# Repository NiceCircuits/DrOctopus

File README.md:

DrOctopus
=========

Art project

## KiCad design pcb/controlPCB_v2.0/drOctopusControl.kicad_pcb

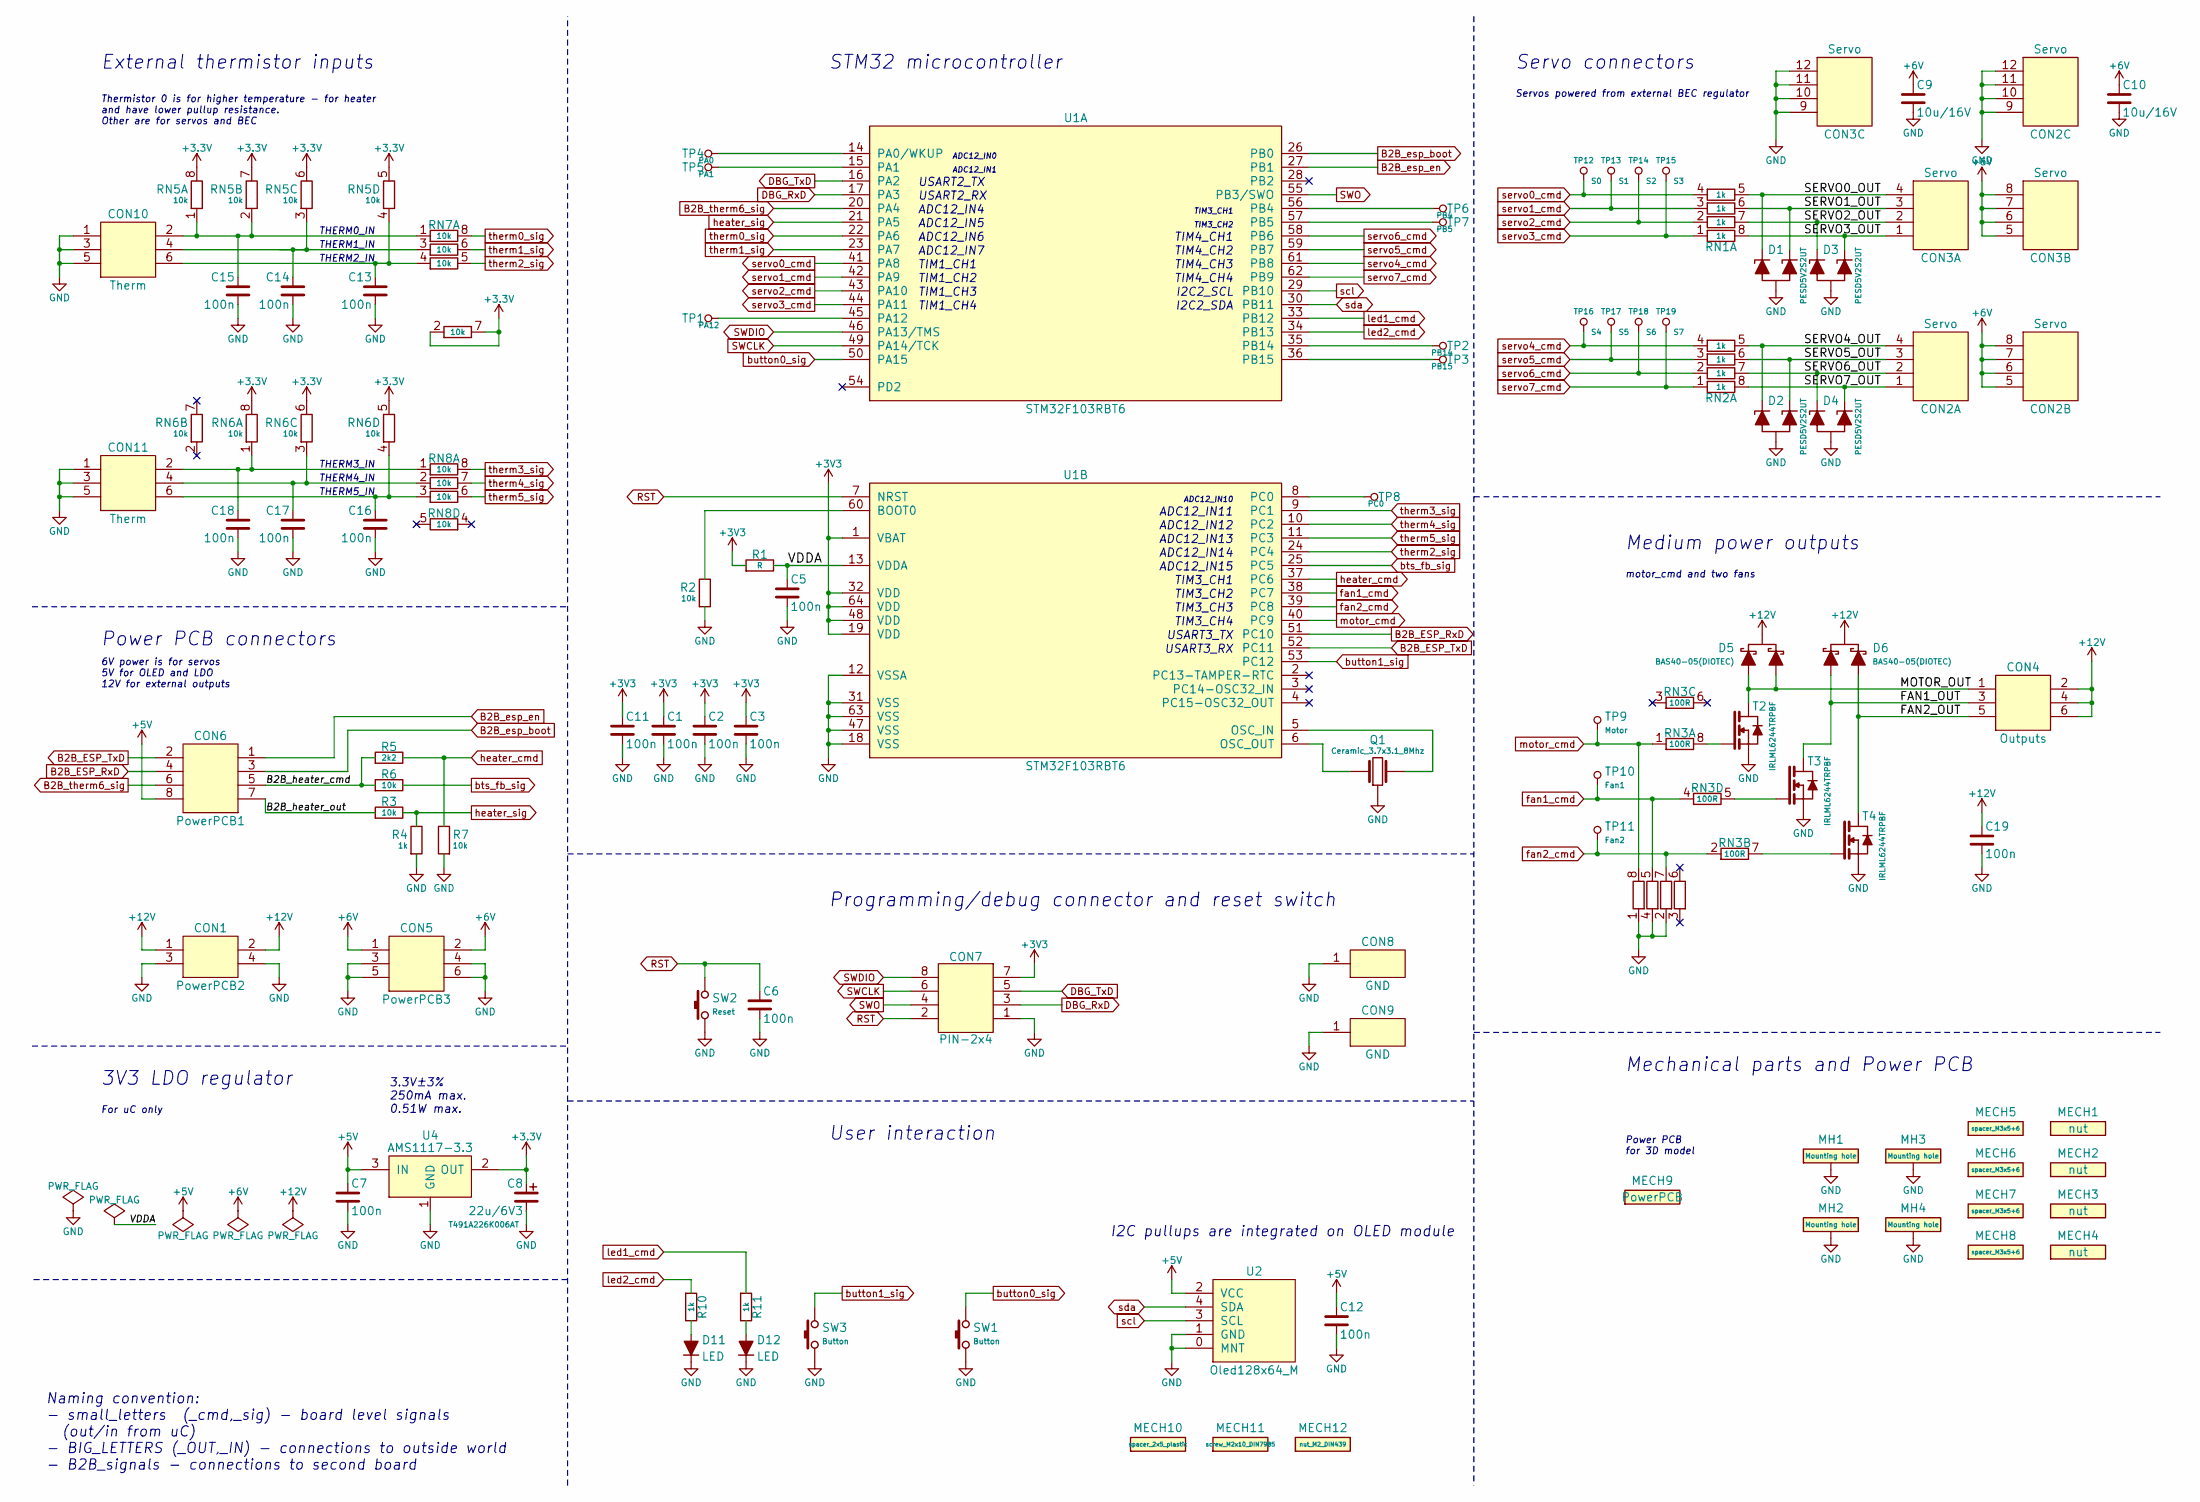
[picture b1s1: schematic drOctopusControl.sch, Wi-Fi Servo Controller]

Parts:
C1, C2, C3, C5, C6, C7, C11, C12, C13, C14, C15, C16, C17, C18, C19: 100n; 0603_N
C8: 22u/6V3; Tantal_A_N
C9, C10: 10u/16V; 0805_N
CON1: PowerPCB2; PIN-2x2_F_N
CON2, CON3: Servo; PIN-3x4_N
CON4: Outputs; PIN-2x3_N
CON5: PowerPCB3; PIN-2x3_F_N
CON6: PowerPCB1; PIN-2x4_F_N
CON7: PIN-2x4; PIN-2x4_N
CON8, CON9: GND; PIN-1x1_L
CON10, CON11: Therm; PIN-2x3_N
D1, D2, D3, D4: PESD5V2S2UT; SOT23-3_N
D5, D6: BAS40-05(DIOTEC); SOT23-3_N
D11, D12: LED; 0805_N
MECH1, MECH2, MECH3, MECH4: nut; nut_M3_DIN985
MECH5, MECH6, MECH7, MECH8: spacer_M3x5+6
MECH9: PowerPCB; dummy
MECH10: spacer_2x5_plastic
MECH11: screw_M2x10_DIN7985
MECH12: nut_M2_DIN439
MH1, MH2, MH3, MH4: Mounting hole; mounting_hole_3.2_7.5_plated_vias
Q1: Ceramic_3.7x3.1_8Mhz; 3.7x3.1_N
R1: R; 0603_R_N
R2, R3, R6, R7: 10k; 0603_R_N
R4, R10, R11: 1k; 0603_R_N
R5: 2k2; 0603_R_N
RN1, RN2: 1k; 4x0603_N
RN3: 100R; 4x0603_N
RN4, RN5, RN6, RN7, RN8: 10k; 4x0603_N
SW1, SW3: Button; MicroswitchSmd6x4_N
SW2: Reset; MicroswitchSmd6x4_N
T2, T3, T4: IRLML6244TRPBF; SOT23-3_N
TP1: PA12; TP_1mm
TP2: PB14; TP_1mm
TP3: PB15; TP_1mm
TP4: PA0; TP_1mm
TP5: PA1; TP_1mm
TP6: PB4; TP_1mm
TP7: PB5; TP_1mm
TP8: PC0; TP_1mm
TP9: Motor; TP_1mm
TP10: Fan1; TP_1mm
TP11: Fan2; TP_1mm
TP12: S0; TP_1mm
TP13: S1; TP_1mm
TP14: S2; TP_1mm
TP15: S3; TP_1mm
TP16: S4; TP_1mm
TP17: S5; TP_1mm
TP18: S6; TP_1mm
TP19: S7; TP_1mm
U1: STM32F103RBT6; QFP-64-0.5_N
U2: Oled128x64_M; Oled128x64_M_5.08N
U4: AMS1117-3.3; SOT223_N

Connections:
+5V: C7.1, C12.1, CON6.8, U2.2 (VCC), U4.3 (IN)
+6V: C9.1, C10.1, CON2.5 (1), CON2.6 (2), CON2.7 (3), CON2.8 (4), CON3.5 (1), CON3.6 (2), CON3.7 (3), CON3.8 (4), CON5.1, CON5.2
+12V: C19.1, CON1.1, CON1.2, CON4.2, CON4.4, CON4.6, D5.3 (C), D6.3 (C)
/B2B_heater_cmd: CON6.5, R5.1, R6.1
/B2B_heater_out: CON6.7, R3.1
/FAN1_OUT: CON4.3, D6.2 (A2), T3.3 (D)
/FAN2_OUT: CON4.5, D6.1 (A1), T4.3 (D)
/MOTOR_OUT: CON4.1, D5.1 (A1), D5.2 (A2), T2.3 (D)
/SERVO0_OUT: CON3.4, D1.2 (C2), RN1.5 (2)
/SERVO1_OUT: CON3.3, D1.1 (C1), RN1.6 (2)
/SERVO2_OUT: CON3.2, D3.2 (C2), RN1.7 (2)
/SERVO3_OUT: CON3.1, D3.1 (C1), RN1.8 (2)
/SERVO4_OUT: CON2.4, D2.2 (C2), RN2.5 (2)
/SERVO5_OUT: CON2.3, D2.1 (C1), RN2.6 (2)
/SERVO6_OUT: CON2.2, D4.2 (C2), RN2.7 (2)
/SERVO7_OUT: CON2.1, D4.1 (C1), RN2.8 (2)
/VDDA: C5.1, R1.2, U1.13 (VDDA)
B2B_ESP_RxD: CON6.4, U1.51 (PC10)
B2B_ESP_TxD: CON6.2, U1.52 (PC11)
B2B_esp_boot: CON6.3, U1.26 (PB0)
B2B_esp_en: CON6.1, U1.27 (PB1)
B2B_therm6_sig: CON6.6, U1.20 (PA4)
DBG_RxD: CON7.3, U1.17 (PA3)
DBG_TxD: CON7.5, U1.16 (PA2)
GND: C1.2, C2.2, C3.2, C5.2, C6.2, C7.2, C8.2, C9.2, C10.2, C11.2, C12.2, C13.2, C14.2, C15.2, C16.2, C17.2, C18.2, C19.2, CON1.3, CON1.4, CON2.9 (1), CON2.10 (2), CON2.11 (3), CON2.12 (4), CON3.9 (1), CON3.10 (2), CON3.11 (3), CON3.12 (4), CON5.3, CON5.4, CON5.5, CON5.6, CON7.1, CON8.1, CON9.1, CON10.1, CON10.3, CON10.5, CON11.1, CON11.3, CON11.5, D1.3 (A), D2.3 (A), D3.3 (A), D4.3 (A), D11.1 (A), D12.1 (A), MH1.1, MH2.1, MH3.1, MH4.1, Q1.2, R2.1, R4.1, R7.1, RN4.1, RN4.2 (1), RN4.4 (1), SW1.1, SW2.1, SW3.1, T2.2 (S), T3.2 (S), T4.2 (S), U1.12 (VSSA), U1.18 (VSS), U1.31 (VSS), U1.47 (VSS), U1.63 (VSS), U2.0 (MNT), U2.1 (GND), U4.1 (GND)
unnamed: C13.1, CON10.6, RN5.4 (1), RN7.4 (1)
unnamed: C14.1, CON10.4, RN5.3 (1), RN7.3 (1)
unnamed: C15.1, CON10.2, RN5.1, RN5.2 (1), RN7.1
unnamed: C16.1, CON11.6, RN6.4 (1), RN8.3 (1)
unnamed: C17.1, CON11.4, RN6.3 (1), RN8.2 (1)
unnamed: C18.1, CON11.2, RN6.1, RN8.1
unnamed: D11.2 (C), R10.2
unnamed: D12.2 (C), R11.2
unnamed: Q1.1, U1.6 (OSC_OUT)
unnamed: Q1.3, U1.5 (OSC_IN)
unnamed: R2.2, U1.60 (BOOT0)
unnamed: RN3.5 (2), T3.1 (G)
unnamed: RN3.7 (2), T4.1 (G)
unnamed: RN3.8 (2), T2.1 (G)
unnamed: TP1.1, U1.45 (PA12)
unnamed: TP2.1, U1.35 (PB14)
unnamed: TP3.1, U1.36 (PB15)
unnamed: TP4.1, U1.14 (PA0/WKUP)
unnamed: TP5.1, U1.15 (PA1)
unnamed: TP6.1, U1.56 (PB4)
unnamed: TP7.1, U1.57 (PB5)
unnamed: TP8.1, U1.8 (PC0)
RST: C6.1, CON7.2, SW2.2, U1.7 (NRST)
SWCLK: CON7.6, U1.49 (PA14/TCK)
SWDIO: CON7.8, U1.46 (PA13/TMS)
SWO: CON7.4, U1.55 (PB3/SWO)
bts_fb_sig: R6.2, U1.25 (PC5)
button0_sig: SW1.2, U1.50 (PA15)
button1_sig: SW3.2, U1.53 (PC12)
fan1_cmd: RN3.4 (1), RN4.5 (2), TP10.1, U1.38 (PC7)
fan2_cmd: RN3.2 (1), RN4.7 (2), TP11.1, U1.39 (PC8)
heater_cmd: R5.2, R7.2, U1.37 (PC6)
heater_sig: R3.2, R4.2, U1.21 (PA5)
led1_cmd: R11.1, U1.33 (PB12)
led2_cmd: R10.1, U1.34 (PB13)
motor_cmd: RN3.1, RN4.8 (2), TP9.1, U1.40 (PC9)
scl: U1.29 (PB10), U2.3 (SCL)
sda: U1.30 (PB11), U2.4 (SDA)
servo0_cmd: RN1.4 (1), TP12.1, U1.41 (PA8)
servo1_cmd: RN1.3 (1), TP13.1, U1.42 (PA9)
servo2_cmd: RN1.2 (1), TP14.1, U1.43 (PA10)
servo3_cmd: RN1.1, TP15.1, U1.44 (PA11)
servo4_cmd: RN2.4 (1), TP16.1, U1.61 (PB8)
servo5_cmd: RN2.3 (1), TP17.1, U1.59 (PB7)
servo6_cmd: RN2.2 (1), TP18.1, U1.58 (PB6)
servo7_cmd: RN2.1, TP19.1, U1.62 (PB9)
therm0_sig: RN7.8 (2), U1.22 (PA6)
therm1_sig: RN7.6 (2), U1.23 (PA7)
therm2_sig: RN7.5 (2), U1.24 (PC4)
therm3_sig: RN8.8 (2), U1.9 (PC1)
therm4_sig: RN8.7 (2), U1.10 (PC2)
therm5_sig: RN8.6 (2), U1.11 (PC3)

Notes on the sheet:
3.3V±3% 250mA max. 0.51W max.
ADC12_IN4
ADC12_IN5
ADC12_IN6
ADC12_IN7
ADC12_IN14
ADC12_IN15
ADC12_IN10
ADC12_IN11
ADC12_IN12
ADC12_IN13
USART2_TX
USART2_RX
I2C2_SCL
I2C2_SDA
TIM3_CH1
TIM3_CH2
TIM3_CH3
TIM3_CH4
TIM1_CH1
TIM1_CH2
TIM1_CH3
TIM1_CH4
USART3_TX
USART3_RX
TIM4_CH1
TIM4_CH2
TIM4_CH3
TIM4_CH4
THERM0_IN
THERM1_IN
THERM2_IN
THERM3_IN
THERM4_IN
THERM5_IN
External thermistor inputs
Thermistor 0 is for higher temperature - for heater and have lower pullup resistance. Other are for servos and BEC
Power PCB connectors
6V power is for servos 5V for OLED and LDO 12V for external outputs
3V3 LDO regulator

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
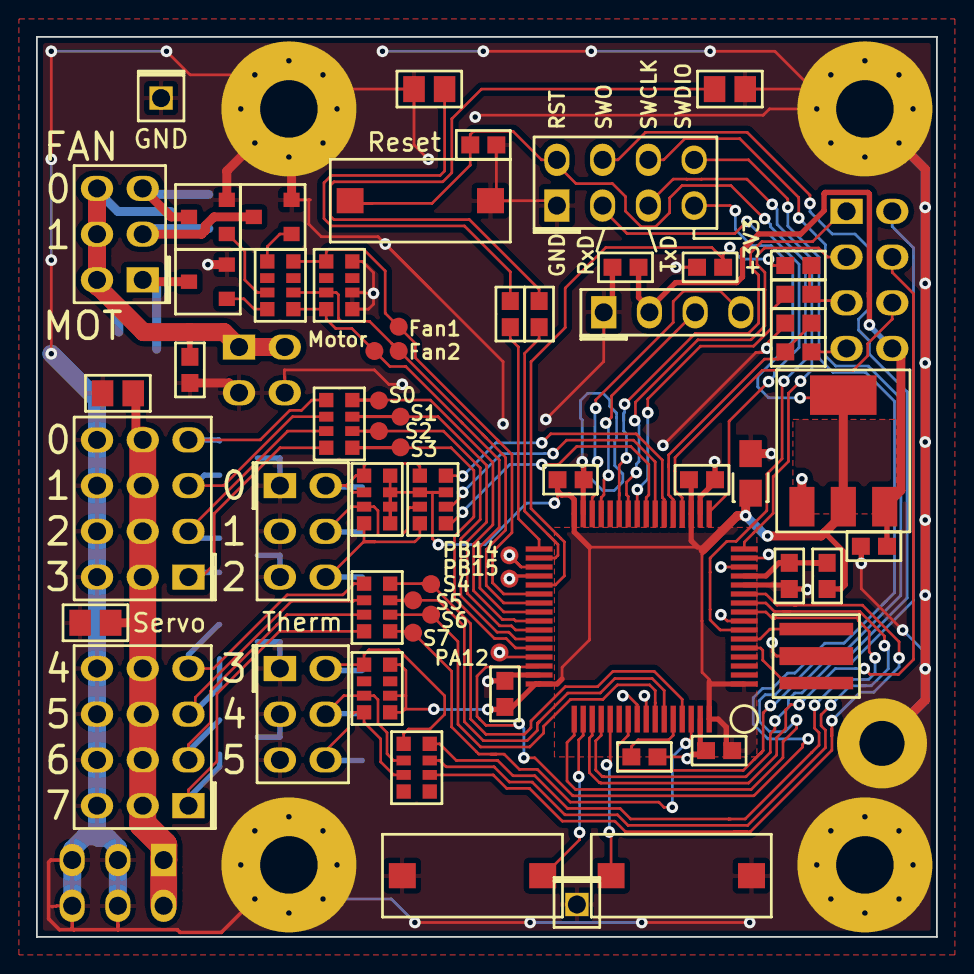
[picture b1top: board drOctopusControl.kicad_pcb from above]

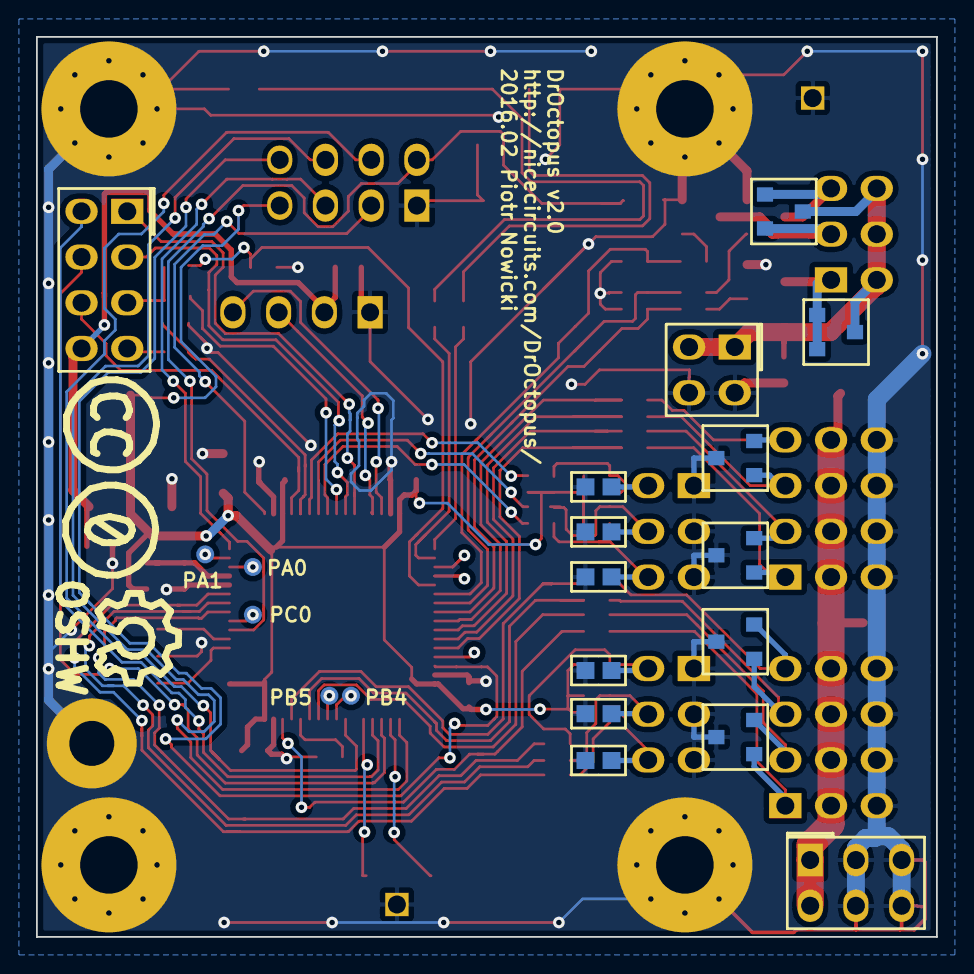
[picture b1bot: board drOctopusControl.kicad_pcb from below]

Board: 2 copper layers, 50.0 x 50.0 mm, 101 parts (27 on the bottom side), 78 nets.

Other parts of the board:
SYM: Symbol_OSHW-Logo_SilkScreen_07Jul2012; Symbol_OSHW-Logo_SilkScreen
Sym: Symbol_CreativeCommonsPublicDomain_SilkScreenTop_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; Symbol_CreativeCommonsPublicDomain_SilkScreenTop_SmallMinim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

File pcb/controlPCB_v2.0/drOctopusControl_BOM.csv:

Reference, Value, Footprint, Datasheet
RN1,1k,4x0603_N,
CON3,Servo,nicePinheaders:PIN-3x4_N,
CON2,Servo,nicePinheaders:PIN-3x4_N,
RN2,1k,4x0603_N,
U4,AMS1117-3.3,SOT223_N,
C7,100n,0603_N,
D1,PESD5V2S2UT,SOT23-3_N,
D3,PESD5V2S2UT,SOT23-3_N,
D2,PESD5V2S2UT,SOT23-3_N,
D4,PESD5V2S2UT,SOT23-3_N,
C9,10u/16V,0805_N,
C10,10u/16V,0805_N,
MH1,Mounting hole,mounting_hole_3.2_7.5_plated_vias,
C8,22u/6V3,Tantal_A_N,T491A226K006AT
MH2,Mounting hole,mounting_hole_3.2_7.5_plated_vias,
MH3,Mounting hole,mounting_hole_3.2_7.5_plated_vias,
MH4,Mounting hole,mounting_hole_3.2_7.5_plated_vias,
MECH1,nut,nut_M3_DIN985,
MECH2,nut,nut_M3_DIN985,
MECH3,nut,nut_M3_DIN985,
MECH4,nut,nut_M3_DIN985,
MECH5,spacer_M3x5+6,spacer_M3x5+6,
MECH6,spacer_M3x5+6,spacer_M3x5+6,
MECH7,spacer_M3x5+6,spacer_M3x5+6,
MECH8,spacer_M3x5+6,spacer_M3x5+6,
R10,1k,0603_R_N,
R11,1k,0603_R_N,
D12,LED,0805_N,
D11,LED,0805_N,
MECH9,PowerPCB,niceMechanical:dummy,
CON1,PowerPCB2,PIN-2x2_F_N,
CON5,PowerPCB3,PIN-2x3_F_N,
CON6,PowerPCB1,PIN-2x4_F_N,
CON10,Therm,PIN-2x3_N,
CON11,Therm,PIN-2x3_N,
CON4,Outputs,PIN-2x3_N,
D6,BAS40-05(DIOTEC),SOT23-3_N,
D5,BAS40-05(DIOTEC),SOT23-3_N,
RN3,100R,4x0603_N,
U2,Oled128x64_M,niceModules:Oled128x64_M_5.08N,
C1,100n,0603_N,
C2,100n,0603_N,
C3,100n,0603_N,
C5,100n,0603_N,
R1,R,0603_R_N,
U1,STM32F103RBT6,QFP-64-0.5_N,
C11,100n,0603_N,
C6,100n,0603_N,
Q1,Ceramic_3.7x3.1_8Mhz,3.7x3.1_N,
C15,100n,0603_N,
C14,100n,0603_N,
C13,100n,0603_N,
RN5,10k,4x0603_N,
C18,100n,0603_N,
C17,100n,0603_N,
C16,100n,0603_N,
RN6,10k,4x0603_N,
T3,IRLML6244TRPBF,SOT23-3_N,
T2,IRLML6244TRPBF,SOT23-3_N,
T4,IRLML6244TRPBF,SOT23-3_N,
SW1,Button,MicroswitchSmd6x4_N,
SW2,Reset,MicroswitchSmd6x4_N,
C12,100n,0603_N,
RN7,10k,4x0603_N,
RN8,10k,4x0603_N,
CON7,PIN-2x4,PIN-2x4_N,
C19,100n,0603_N,
R3,10k,0603_R_N,
R6,10k,0603_R_N,
R5,2k2,0603_R_N,
RN4,10k,4x0603_N,
R2,10k,0603_R_N,
R4,1k,0603_R_N,
R7,10k,0603_R_N,
TP2,PB14,pnConnector:TP_1mm,
TP3,PB15,pnConnector:TP_1mm,
TP4,PA0,pnConnector:TP_1mm,
TP5,PA1,pnConnector:TP_1mm,
TP8,PC0,pnConnector:TP_1mm,
TP6,PB4,pnConnector:TP_1mm,
TP7,PB5,pnConnector:TP_1mm,
TP1,PA12,pnConnector:TP_1mm,
CON9,GND,PIN-1x1_L,
CON8,GND,PIN-1x1_L,
TP9,Motor,pnConnector:TP_1mm,
TP10,Fan1,pnConnector:TP_1mm,
TP11,Fan2,pnConnector:TP_1mm,
TP16,S4,pnConnector:TP_1mm,
TP17,S5,pnConnector:TP_1mm,
TP18,S6,pnConnector:TP_1mm,
TP19,S7,pnConnector:TP_1mm,
TP12,S0,pnConnector:TP_1mm,
TP13,S1,pnConnector:TP_1mm,
TP14,S2,pnConnector:TP_1mm,
TP15,S3,pnConnector:TP_1mm,
SW3,Button,MicroswitchSmd6x4_N,
MECH10,spacer_2x5_plastic,niceMechanical:spacer_2x5_plastic,
MECH11,screw_M2x10_DIN7985,niceMechanical:screw_M2x10_DIN7985,
MECH12,nut_M2_DIN439,niceMechanical:nut_M2_DIN439,

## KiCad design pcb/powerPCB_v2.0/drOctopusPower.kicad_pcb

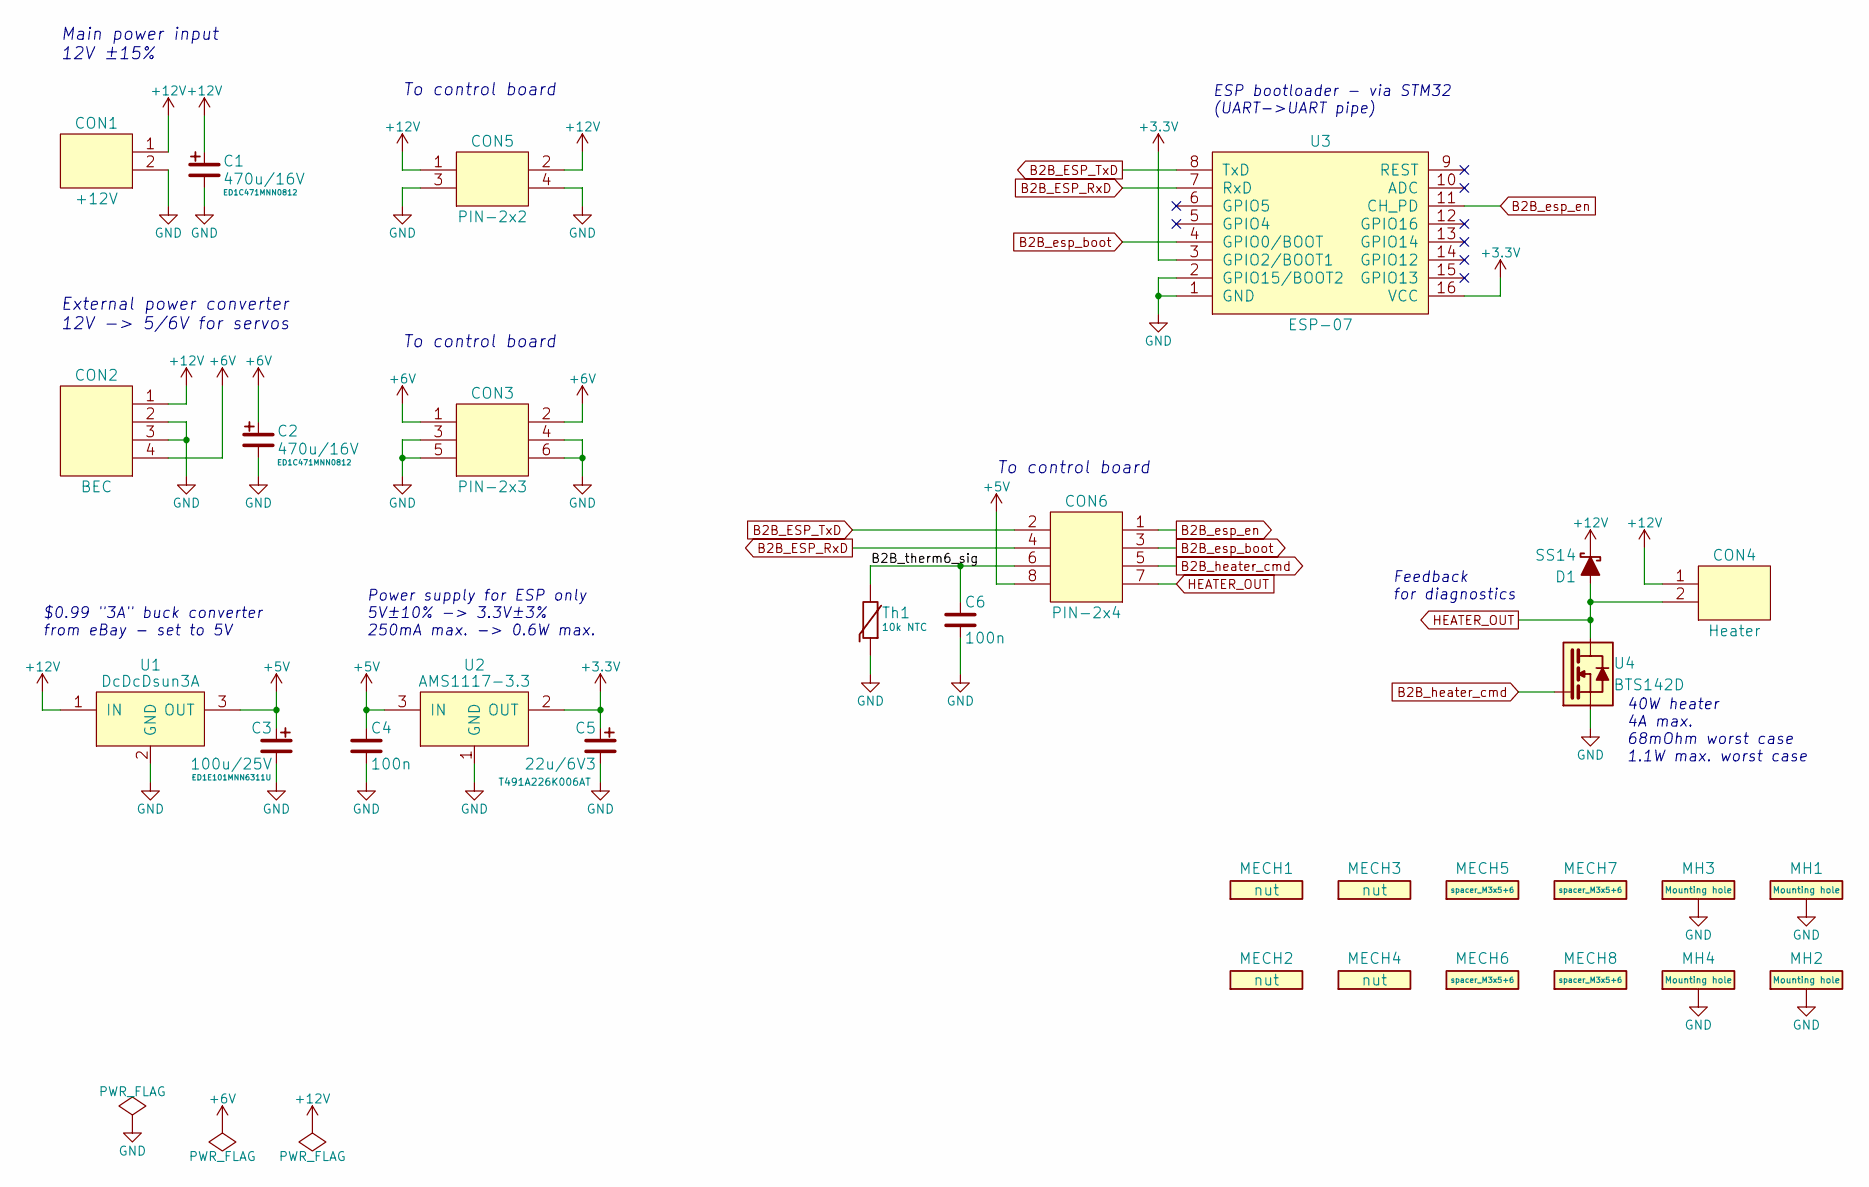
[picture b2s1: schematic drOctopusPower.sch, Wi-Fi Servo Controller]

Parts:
C1, C2: 470u/16V; Cpol_8.0_12.0_HR_N
C3: 100u/25V; Cpol_6.3_11.0_HR_N
C4, C6: 100n; 0603_N
C5: 22u/6V3; Tantal_A_N
CON1: +12V; EDG-5.08mm-2_N
CON2: BEC; EDG-5.08mm-4_N
CON3: PIN-2x3; PIN-2x3_N
CON4: Heater; EDG-5.08mm-2_N
CON5: PIN-2x2; PIN-2x2_N
CON6: PIN-2x4; PIN-2x4_N
D1: SS14; SMA_N
MECH1, MECH2, MECH3, MECH4: nut; nut_M3_DIN985
MECH5, MECH6, MECH7, MECH8: spacer_M3x5+6
MH1, MH2, MH3, MH4: Mounting hole; mounting_hole_3.2_7.5_plated_vias
Th1: 10k NTC; 0603_N
U1: DcDcDsun3A; DcDcDsun3A_5.08N
U2: AMS1117-3.3; SOT223_N
U3: ESP-07; ESP-07_N
U4: BTS142D; D-PAK_N

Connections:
+3V3: C5.1, U2.2 (OUT), U3.3 (GPIO2/BOOT1), U3.16 (VCC)
+5V: C3.1, C4.1, CON6.8, U1.3 (OUT), U2.3 (IN)
+6V: C2.1, CON2.4, CON3.1, CON3.2
+12V: C1.1, CON1.1, CON2.1, CON4.1, CON5.1, CON5.2, D1.1 (A), U1.1 (IN)
/B2B_therm6_sig: C6.1, CON6.6, Th1.2
B2B_ESP_RxD: CON6.4, U3.7 (RxD)
B2B_ESP_TxD: CON6.2, U3.8 (TxD)
B2B_esp_boot: CON6.3, U3.4 (GPIO0/BOOT)
B2B_esp_en: CON6.1, U3.11 (CH_PD)
B2B_heater_cmd: CON6.5, U4.1 (G)
GND: C1.2, C2.2, C3.2, C4.2, C5.2, C6.2, CON1.2, CON2.2, CON2.3, CON3.3, CON3.4, CON3.5, CON3.6, CON5.3, CON5.4, MH1.1, MH2.1, MH3.1, MH4.1, Th1.1, U1.2 (GND), U2.1 (GND), U3.1 (GND), U3.2 (GPIO15/BOOT2), U4.3 (S)
HEATER_OUT: CON4.2, CON6.7, D1.2 (C), U4.2 (D)

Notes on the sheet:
Power supply for ESP only 5V±10% -> 3.3V±3% 250mA max. -> 0.6W max.
40W heater 4A max. 68mOhm worst case 1.1W max. worst case
Main power input 12V ±15%
External power converter 12V -> 5/6V for servos
$0.99 "3A" buck converter from eBay - set to 5V
ESP bootloader - via STM32 (UART->UART pipe)
Feedback for diagnostics
To control board

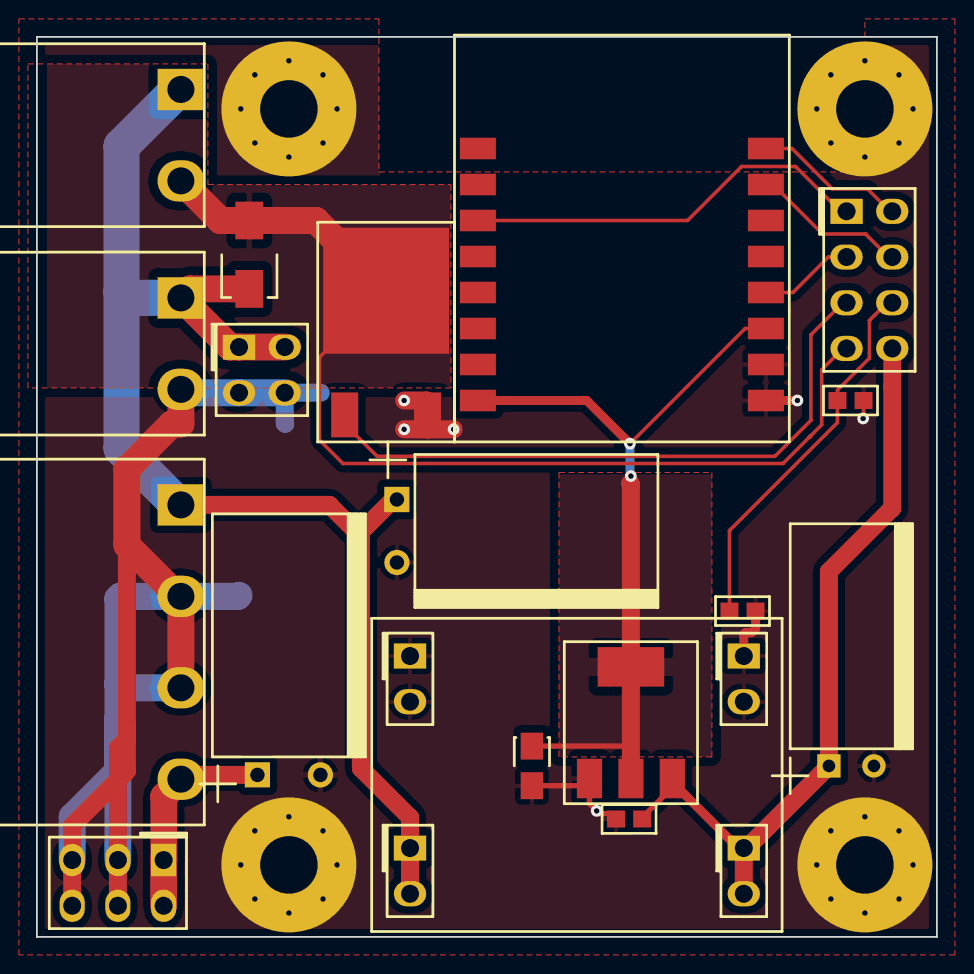
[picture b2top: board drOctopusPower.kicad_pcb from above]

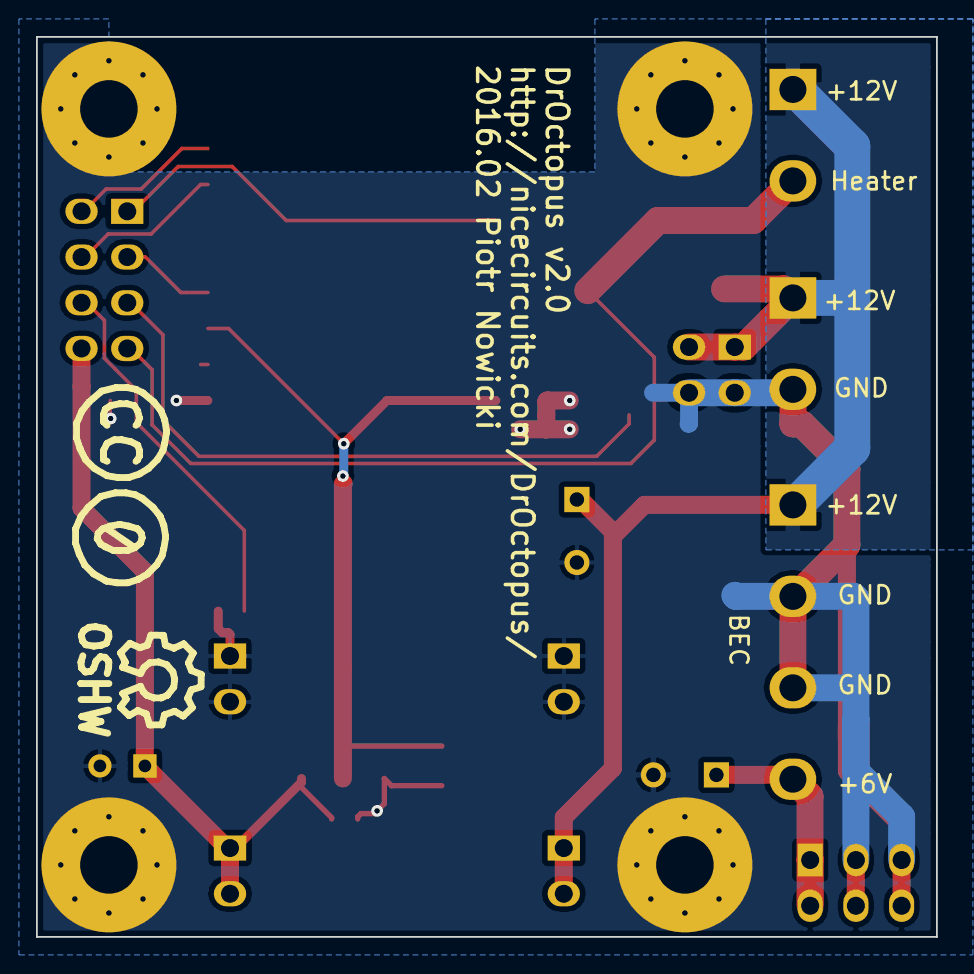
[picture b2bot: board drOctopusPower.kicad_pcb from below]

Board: 2 copper layers, 50.0 x 50.0 mm, 32 parts (6 on the bottom side), 12 nets.

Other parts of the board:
SYM: Symbol_OSHW-Logo_SilkScreen_07Jul2012; Symbol_OSHW-Logo_SilkScreen
Sym: Symbol_CreativeCommonsPublicDomain_SilkScreenTop_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; Symbol_CreativeCommonsPublicDomain_SilkScreenTop_SmallMinim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

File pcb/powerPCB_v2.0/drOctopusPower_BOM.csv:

Reference, Value, Footprint, Datasheet
CON2,BEC,EDG-5.08mm-4_N,
CON4,Heater,EDG-5.08mm-2_N,
CON1,+12V,EDG-5.08mm-2_N,
U2,AMS1117-3.3,SOT223_N,
C4,100n,0603_N,
C1,470u/16V,niceRLC:Cpol_8.0_12.0_HR_N,ED1C471MNN0812
D1,SS14,SMA_N,
MH1,Mounting hole,mounting_hole_3.2_7.5_plated_vias,
C5,22u/6V3,Tantal_A_N,T491A226K006AT
MH2,Mounting hole,mounting_hole_3.2_7.5_plated_vias,
MH3,Mounting hole,mounting_hole_3.2_7.5_plated_vias,
MH4,Mounting hole,mounting_hole_3.2_7.5_plated_vias,
MECH1,nut,nut_M3_DIN985,
MECH2,nut,nut_M3_DIN985,
MECH3,nut,nut_M3_DIN985,
MECH4,nut,nut_M3_DIN985,
MECH5,spacer_M3x5+6,spacer_M3x5+6,
MECH6,spacer_M3x5+6,spacer_M3x5+6,
MECH7,spacer_M3x5+6,spacer_M3x5+6,
MECH8,spacer_M3x5+6,spacer_M3x5+6,
U3,ESP-07,ESP-07_N,
C3,100u/25V,niceRLC:Cpol_6.3_11.0_HR_N,ED1E101MNN6311U
U1,DcDcDsun3A,niceModules:DcDcDsun3A_5.08N,
C2,470u/16V,niceRLC:Cpol_8.0_12.0_HR_N,ED1C471MNN0812
CON3,PIN-2x3,PIN-2x3_N,
CON5,PIN-2x2,PIN-2x2_N,
CON6,PIN-2x4,nicePinheaders:PIN-2x4_N,
Th1,10k NTC,0603_N,
U4,BTS142D,D-PAK_N,
C6,100n,0603_N,

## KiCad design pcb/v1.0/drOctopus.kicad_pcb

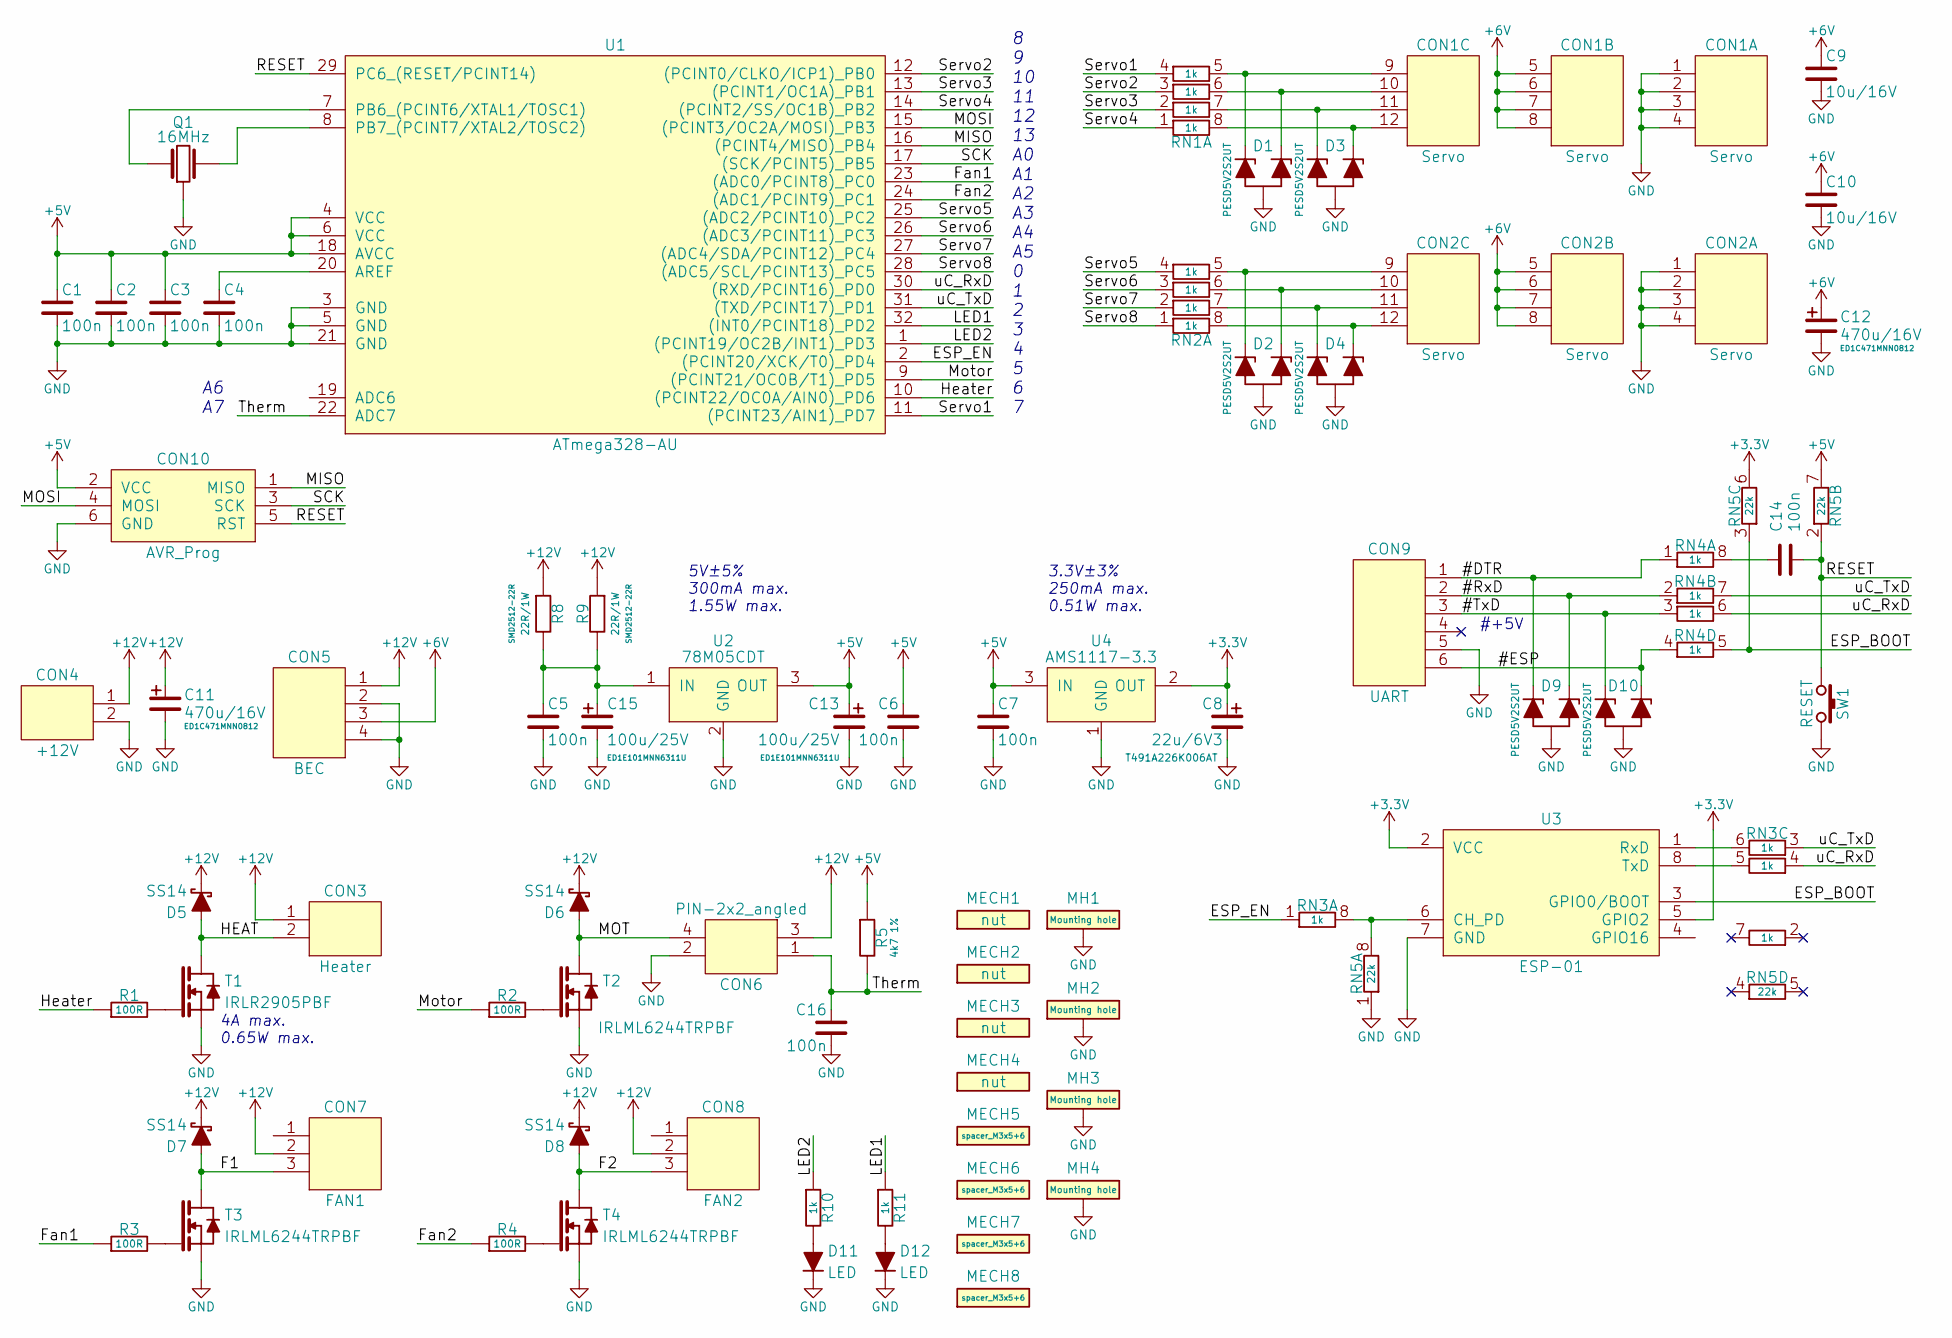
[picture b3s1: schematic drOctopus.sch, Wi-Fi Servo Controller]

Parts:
C1, C2, C3, C4, C5, C6, C7, C14, C16: 100n; 0603_N
C8: 22u/6V3; Tantal_A_N
C9, C10: 10u/16V; 0805_N
C11, C12: 470u/16V; Cpol_8.0_12.0_M
C13, C15: 100u/25V; Cpol_6.3_11.0_N
CON1, CON2: Servo; PIN-3x4_angled_N
CON3: Heater; EDG-5.08mm-2_N
CON4: +12V; EDG-5.08mm-2_N
CON5: BEC; EDG-5.08mm-4_N
CON6: PIN-2x2_angled; PIN-2x2_angled_N
CON7: FAN1; PIN-1x3_M
CON8: FAN2; PIN-1x3_M
CON9: UART; PIN-1x6_angled_N
CON10: AVR_Prog; PIN-2x3_N
D1, D2, D3, D4, D9, D10: PESD5V2S2UT; SOT23-3_N
D5, D6, D7, D8: SS14; SMA_N
D11, D12: LED; 0805_N
MECH1, MECH2, MECH3, MECH4: nut; nut_M3_DIN985
MECH5, MECH6, MECH7, MECH8: spacer_M3x5+6
MH1, MH2, MH3, MH4: Mounting hole; mounting_hole_3.2_7.5_plated_vias
Q1: 16MHz; 3.7x3.1_N
R1, R2, R3, R4: 100R; 0603_N
R5: 4k7 1%; 0603_N
R8, R9: 22R/1W; 2512_N
R10, R11: 1k; 0603_N
RN1, RN2, RN3, RN4: 1k; 4x0603_N
RN5: 22k; 4x0603_N
SW1: RESET; MicroswitchSmd-4.3_N
T1: IRLR2905PBF; D-PAK_N
T2, T3, T4: IRLML6244TRPBF; SOT23-3_N
U1: ATmega328-AU; QFP-32-0.8_M
U2: 78M05CDT; D-PAK_N
U3: ESP-01; ESP-01_N_socket
U4: AMS1117-3.3; SOT223_N

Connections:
+3V3: C8.1, RN5.6 (2), U3.2 (VCC), U3.5 (GPIO2), U4.2 (OUT)
+5V: C1.1, C2.1, C3.1, C6.1, C7.1, C13.1, CON10.2 (VCC), R5.1, RN5.7 (2), U1.4 (VCC), U1.6 (VCC), U1.18 (AVCC), U2.3 (OUT), U4.3 (IN)
+6V: C9.1, C10.1, C12.1, CON1.5 (1), CON1.6 (2), CON1.7 (3), CON1.8 (4), CON2.5 (1), CON2.6 (2), CON2.7 (3), CON2.8 (4), CON5.3
+12V: C11.1, CON3.1, CON4.1, CON5.1, CON6.3, CON7.2, CON8.2, D5.1 (A), D6.1 (A), D7.1 (A), D8.1 (A), R8.1, R9.1
/#DTR: CON9.1, D9.1 (C1), RN4.1
/#ESP: CON9.6, D10.2 (C2), RN4.4 (1)
/#RxD: CON9.2, D9.2 (C2), RN4.2 (1)
/#TxD: CON9.3, D10.1 (C1), RN4.3 (1)
/ESP_BOOT: RN4.5 (2), RN5.3 (1), U3.3 (GPIO0/BOOT)
/ESP_EN: RN3.1, U1.2 ((PCINT20/XCK/T0)_PD4)
/F1: CON7.3, D7.2 (C), T3.3 (D)
/F2: CON8.3, D8.2 (C), T4.3 (D)
/Fan1: R3.1, U1.23 ((ADC0/PCINT8)_PC0)
/Fan2: R4.1, U1.24 ((ADC1/PCINT9)_PC1)
/HEAT: CON3.2, D5.2 (C), T1.2 (D)
/Heater: R1.1, U1.10 ((PCINT22/OC0A/AIN0)_PD6)
/LED1: R11.1, U1.32 ((INT0/PCINT18)_PD2)
/LED2: R10.1, U1.1 ((PCINT19/OC2B/INT1)_PD3)
/MISO: CON10.1 (MISO), U1.16 ((PCINT4/MISO)_PB4)
/MOSI: CON10.4 (MOSI), U1.15 ((PCINT3/OC2A/MOSI)_PB3)
/MOT: CON6.4, D6.2 (C), T2.3 (D)
/Motor: R2.1, U1.9 ((PCINT21/OC0B/T1)_PD5)
/RESET: C14.2, CON10.5 (RST), RN5.2 (1), SW1.2, U1.29 (PC6_(RESET/PCINT14))
/SCK: CON10.3 (SCK), U1.17 ((SCK/PCINT5)_PB5)
/Servo1: RN1.4 (1), U1.11 ((PCINT23/AIN1)_PD7)
/Servo2: RN1.3 (1), U1.12 ((PCINT0/CLKO/ICP1)_PB0)
/Servo3: RN1.2 (1), U1.13 ((PCINT1/OC1A)_PB1)
/Servo4: RN1.1, U1.14 ((PCINT2/SS/OC1B)_PB2)
/Servo5: RN2.4 (1), U1.25 ((ADC2/PCINT10)_PC2)
/Servo6: RN2.3 (1), U1.26 ((ADC3/PCINT11)_PC3)
/Servo7: RN2.2 (1), U1.27 ((ADC4/SDA/PCINT12)_PC4)
/Servo8: RN2.1, U1.28 ((ADC5/SCL/PCINT13)_PC5)
/Therm: C16.1, CON6.1, R5.2, U1.22 (ADC7)
/uC_RxD: RN3.4 (1), RN4.6 (2), U1.30 ((RXD/PCINT16)_PD0)
/uC_TxD: RN3.3 (1), RN4.7 (2), U1.31 ((TXD/PCINT17)_PD1)
GND: C1.2, C2.2, C3.2, C4.2, C5.2, C6.2, C7.2, C8.2, C9.2, C10.2, C11.2, C12.2, C13.2, C15.2, C16.2, CON1.1, CON1.2, CON1.3, CON1.4, CON2.1, CON2.2, CON2.3, CON2.4, CON4.2, CON5.2, CON5.4, CON6.2, CON9.5, CON10.6 (GND), D1.3 (A), D2.3 (A), D3.3 (A), D4.3 (A), D9.3 (A), D10.3 (A), D11.1 (A), D12.1 (A), MH1.1, MH2.1, MH3.1, MH4.1, Q1.2, RN5.1, SW1.1, T1.3 (S), T2.2 (S), T3.2 (S), T4.2 (S), U1.3 (GND), U1.5 (GND), U1.21 (GND), U2.2 (GND), U3.7 (GND), U4.1 (GND)
unnamed: C4.1, U1.20 (AREF)
unnamed: C14.1, RN4.8 (2)
unnamed: C5.1, C15.1, R8.2, R9.2, U2.1 (IN)
unnamed: CON1.9 (1), D1.1 (C1), RN1.5 (2)
unnamed: CON1.10 (2), D1.2 (C2), RN1.6 (2)
unnamed: CON1.11 (3), D3.1 (C1), RN1.7 (2)
unnamed: CON1.12 (4), D3.2 (C2), RN1.8 (2)
unnamed: CON2.9 (1), D2.1 (C1), RN2.5 (2)
unnamed: CON2.10 (2), D2.2 (C2), RN2.6 (2)
unnamed: CON2.11 (3), D4.1 (C1), RN2.7 (2)
unnamed: CON2.12 (4), D4.2 (C2), RN2.8 (2)
unnamed: D11.2 (C), R10.2
unnamed: D12.2 (C), R11.2
unnamed: Q1.1, U1.7 (PB6_(PCINT6/XTAL1/TOSC1))
unnamed: Q1.3, U1.8 (PB7_(PCINT7/XTAL2/TOSC2))
unnamed: R1.2, T1.1 (G)
unnamed: R2.2, T2.1 (G)
unnamed: R3.2, T3.1 (G)
unnamed: R4.2, T4.1 (G)
unnamed: RN3.5 (2), U3.8 (TxD)
unnamed: RN3.6 (2), U3.1 (RxD)
unnamed: RN3.8 (2), RN5.8 (2), U3.6 (CH_PD)

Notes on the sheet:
#+5V
3.3V±3% 250mA max. 0.51W max.
5V±5% 300mA max. 1.55W max.
4A max. 0.65W max.
8 9 10 11 12 13 A0 A1 A2 A3 A4 A5 0 1 2 3 4 5 6 7
A6 A7
